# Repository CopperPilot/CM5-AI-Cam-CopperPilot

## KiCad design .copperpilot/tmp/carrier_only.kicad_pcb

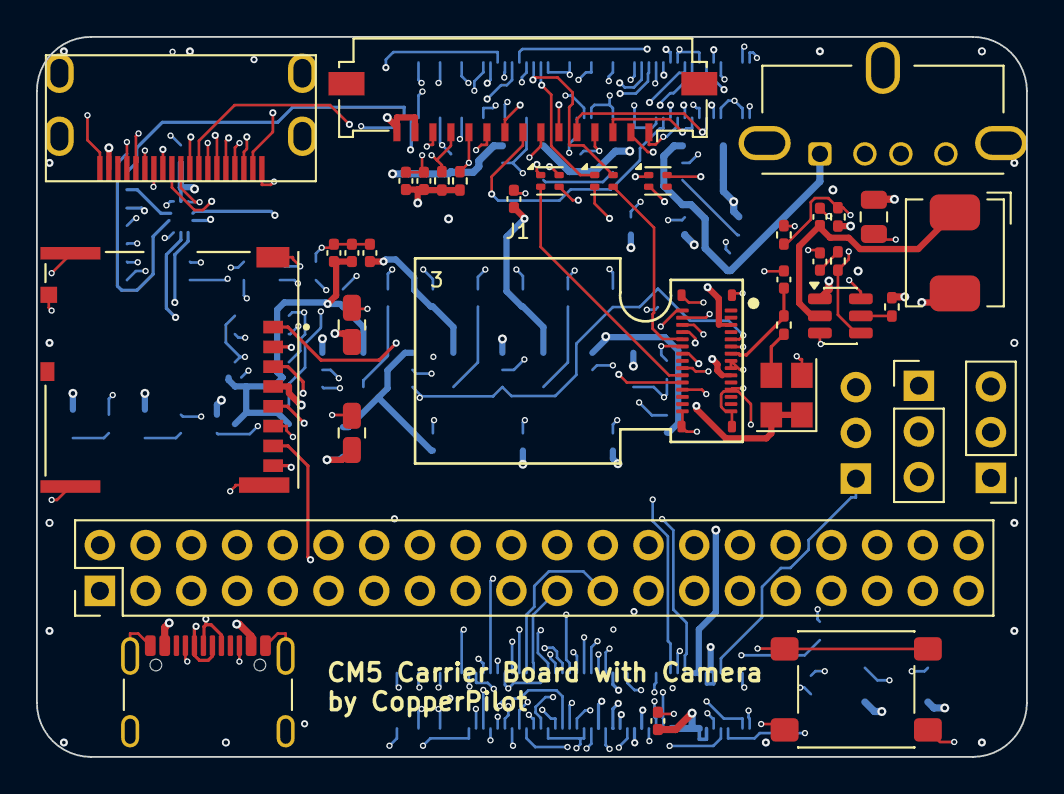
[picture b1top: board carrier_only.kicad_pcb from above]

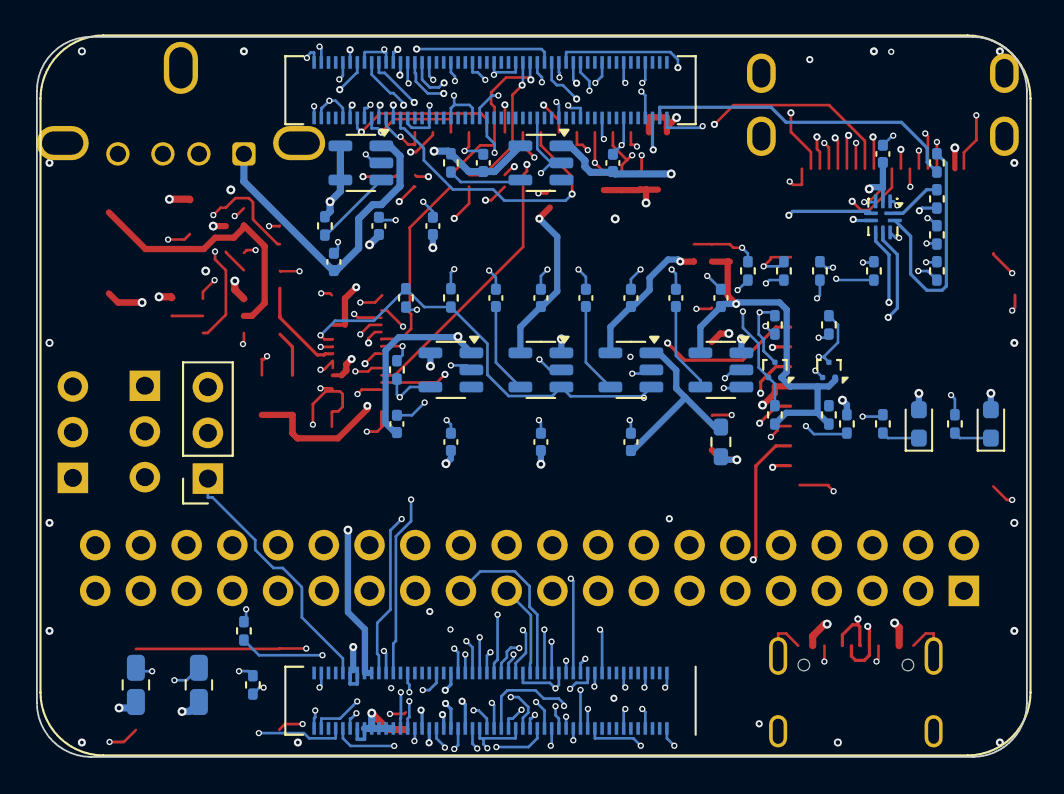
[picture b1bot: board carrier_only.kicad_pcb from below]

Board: 6 copper layers, 55.0 x 40.0 mm, 90 parts (54 on the bottom side), 118 nets.

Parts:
C1, C5, C12: 2.2uF; C_0402_1005Metric
C2, C6, C7, C8, C9, C15, C16, C21, C29, C30: 1uF; C_0402_1005Metric
C3, C10, C14: 100nF; C_0402_1005Metric
C4, C11, C22: 10uF; C_0805_2012Metric
C17, C18, C19, C23, C24, C27, C28, C31, C32: 0.1uF; C_0402_1005Metric
C20: 10pF; C_0402_1005Metric
C25, C26: 22uF; C_0805_2012Metric
DSI1: DSI_15P; Molex_200528-0150_1x15-1MP_P1.00mm_Horizontal
FB1: 120R; R_0603_1608Metric
H3, H4, H5: Conn_01x03; PinHeader_1x03_P2.54mm_Vertical
HDMI1: HDMI_Mini_C; HDMI_Mini-C_Molex_47151-0001
J1: Camera_Module_IMX219-D160
J2: USB_A_Vertical; MOLEX_USB_67298-4090
Key1: SW_Push_SPST; SW_SPST_PTS645Sx43SMTR92
L1, L2, L3: MCF1210BF2-900T01; L_CommonModeChoke_Coilank_ACM1210
L5: LED Red; LED_0603_1608Metric
L6: LED Green; LED_0603_1608Metric
L7: 4.7uH; L_Bourns_SRP5030CC
Module1: ComputeModule5-CM5; Raspberry-Pi-5-Compute-Module
PI1: Raspberry_Pi_40Pin_GPIO; PinHeader_2x20_P2.54mm_Vertical
Q1, Q2: DMG1012T; Texas_DRT-3
R1, R17, R22, R24, R29, R31, R32, R33: 0R; R_0402_1005Metric
R2, R3: 5.1k; R_0402_1005Metric
R4, R7, R35, R36: 4.7k; R_0402_1005Metric
R5, R8: 2.2k; R_0402_1005Metric
R10: 22R; R_0402_1005Metric
R11, R14, R30, R34: 10k; R_0402_1005Metric
R12, R13: 1k; R_0402_1005Metric
R15, R19, R20: 100k; R_0402_1005Metric
R16: 10R; R_0402_1005Metric
R21: 20k; R_0402_1005Metric
R28: 47k; R_0402_1005Metric
TF1: Micro_SD_Card_Det; SDCARD_MOLEX_503398-1892
Type_C1: USB_C_Receptacle_USB2.0_16P; USB_C_Receptacle_GCT_USB4105-xx-A_16P_TopMnt_Horizontal
U1: RT9193-28GB; SOT-23-5
U2: RT9193-18GB; SOT-23-5
U3: RT9013-12; SOT-23-5
U4, U7: DIO7003HCST5; SOT-23-5
U5: MP1658GTF-Z; TSOT-23-6
U6: FSUSB42MX; UQFN-10_1.4x1.8mm_P0.4mm
U8: STMPS2171STR; SOT-23-5
X1: OSC_24MHz; Crystal_SMD_3225-4Pin_3.2x2.5mm

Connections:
/1V2: C7.1, C15.1, J1.4, U3.5
/1V8: C6.1, C9.1, C16.1, J1.3, Q1.1, Q2.1, R5.1, R8.1, U2.5, X1.1, X1.4
/2V8: C2.1, C8.1, J1.10, U1.5
/BT_EN: Module1.91, R32.1
/CAM0_CLK_N: L3.4, Module1.140
/CAM0_CLK_P: L3.1, Module1.142
/CAM0_D0_N: L1.4, Module1.128
/CAM0_D0_P: L1.1, Module1.130
/CAM0_D1_N: L2.4, Module1.134
/CAM0_D1_P: L2.1, Module1.136
/CAM_FB1_OUT: C1.1, FB1.2, U1.1
/CAM_GPIO: Module1.97, R17.1
/CAM_GPIO': J1.5, R15.1, R17.2, U1.3, U2.3, U3.3
/CC1: R3.1, Type_C1.A5
/CC2: R2.1, Type_C1.B5
/CM5_1V8: H5.3, Module1.88, Module1.90
/CM5_3V3: C28.1, H5.1, Module1.84, Module1.86, U6.9
/CM5_5V: C4.1, C11.1, C17.1, C22.1, C23.1, C30.1, Module1.77, Module1.79, Module1.81, Module1.83, Module1.85, Module1.87, PI1.2, PI1.4, R14.2, R19.2, R34.2, Type_C1.A4, Type_C1.A9, Type_C1.B4, Type_C1.B9, U4.5, U5.1, U8.4, U8.5
/CSI_CLK_N: J1.26, L3.3
/CSI_CLK_P: J1.27, L3.2
/CSI_D0_N: J1.23, L1.3
/CSI_D0_P: J1.24, L1.2
/CSI_D1_N: J1.20, L2.3
/CSI_D1_P: J1.21, L2.2
/DSI1_CLK_N: DSI1.5, Module1.187
/DSI1_CLK_P: DSI1.6, Module1.189
/DSI1_D0_N: DSI1.8, Module1.175
/DSI1_D0_P: DSI1.9, Module1.177
/DSI1_D1_N: DSI1.2, Module1.181
/DSI1_D1_P: DSI1.3, Module1.183
/EEPROM_WP: Module1.20, R29.1
/GPIO2: Module1.58, PI1.3
/GPIO3: Module1.56, PI1.5
/GPIO4: Module1.54, PI1.7
/GPIO5: Module1.34, PI1.29
/GPIO6: Module1.30, PI1.31
/GPIO7: Module1.37, PI1.26
/GPIO8: Module1.39, PI1.24
/GPIO9: Module1.40, PI1.21
/GPIO10: Module1.44, PI1.19
/GPIO11: Module1.38, PI1.23
/GPIO12: Module1.31, PI1.32
/GPIO13: Module1.28, PI1.33
/GPIO14: Module1.55, PI1.8
/GPIO15: Module1.51, PI1.10
/GPIO16: Module1.29, PI1.36
/GPIO17: Module1.50, PI1.11
/GPIO18: Module1.49, PI1.12
/GPIO19: Module1.26, PI1.35
/GPIO20: Module1.27, PI1.38
/GPIO21: Key1.1, Module1.25, PI1.40, R11.1
/GPIO22: Module1.46, PI1.15
/GPIO23: Module1.47, PI1.16
/GPIO24: Module1.45, PI1.18
/GPIO25: Module1.41, PI1.22
/GPIO26: Module1.24, PI1.37
/GPIO27: Module1.48, PI1.13
/GPIO_VREF: H5.2, Module1.78, R4.1, R7.1
/HDMI0_CEC: HDMI1.14, Module1.151
/HDMI0_CLK_N: HDMI1.12, Module1.190
/HDMI0_CLK_P: HDMI1.11, Module1.188
/HDMI0_HOTPLUG: HDMI1.19, Module1.153
/HDMI0_SCL: HDMI1.15, Module1.200
/HDMI0_SDA: HDMI1.16, Module1.199
/HDMI0_TX0_N: HDMI1.9, Module1.184
/HDMI0_TX0_P: HDMI1.8, Module1.182
/HDMI0_TX1_N: HDMI1.6, Module1.178
/HDMI0_TX1_P: HDMI1.5, Module1.176
/HDMI0_TX2_N: HDMI1.3, Module1.172
/HDMI0_TX2_P: HDMI1.2, Module1.170
/HDMI_5V: C18.1, HDMI1.18, U4.1
/HDMI_5V_EN: R14.1, U4.4
/ID_SC: Module1.35, PI1.28
/ID_SD: Module1.36, PI1.27
/L5_K: L5.1, R12.1
/L6_K: L6.1, R13.1
/LED_G: Module1.21, R13.2
/MCLK: C20.1, J1.7, R10.2
/MP1658_BST: C24.2, R16.1, U5.4
/MP1658_BST_R: C21.1, R16.2
/MP1658_EN: R19.1, U5.5
/MP1658_FB: R20.2, R21.1, U5.6
/MP1658_SW: C24.1, L7.1, U5.2
/PI_BOOT: H4.1, Module1.93
/PI_GLOBAL_EN: H3.3, Module1.99
/PI_RUN: H3.1, Module1.92
/PWR_3V3: C5.1, C12.1, C19.1, C25.1, C26.1, C27.1, C31.1, DSI1.14, DSI1.15, FB1.1, L5.2, L6.2, L7.2, PI1.1, PI1.17, R11.2, R20.1, R35.1, R36.1, U2.1, U3.1, U7.5
/SCL0: DSI1.11, Module1.80, Q1.3, R4.2, R35.2
/SCL_1V8: J1.29, Q1.2, R5.2
/SDA0: DSI1.12, Module1.82, Q2.3, R7.2, R36.2
/SDA_1V8: J1.30, Q2.2, R8.2
/SD_3.3V: C32.1, TF1.4, U7.1
/SD_CLK: Module1.57, TF1.5
/SD_CMD: Module1.62, TF1.3
/SD_DAT0: Module1.63, TF1.7
/SD_DAT1: Module1.67, TF1.8
/SD_DAT2: Module1.69, TF1.1
/SD_DAT3: Module1.61, TF1.2
/SD_PWREN: Module1.75, R30.1, U7.4
/SD_VDD_Override: Module1.73, R1.1
/U1_BP: C3.1, U1.4
/U2_BP: C10.1, U2.4
/U3_BP: C14.1, U3.4
/USB0_B_N: R22.2, U6.2
/USB0_B_P: R24.2, U6.1
/USB0_ID: Module1.101, R33.1
/USB0_N: Module1.103, R22.1
/USB0_P: Module1.105, R24.1
/USBB_N: Type_C1.A7, Type_C1.B7, U6.4
/USBB_P: Type_C1.A6, Type_C1.B6, U6.5
/USBD0_N: J2.2, U6.6
/USBD0_P: J2.3, U6.7
/USB_5V: C29.1, J2.1, U8.1
/USB_FAULT: R34.1, U8.3
/USB_SEL: H4.3, R28.1, U6.10
/WIFI_EN: Module1.89, R31.1
/X1_OUT: R10.1, X1.3
GND: C1.2, C2.2, C3.2, C4.2, C5.2, C6.2, C7.2, C8.2, C9.2, C10.2, C11.2, C12.2, C14.2, C15.2, C16.2, C17.2, C18.2, C19.2, C20.2, C21.2, C22.2, C23.2, C25.2, C26.2, C27.2, C28.2, C29.2, C30.2, C31.2, C32.2, DSI1.1, DSI1.4, DSI1.7, DSI1.10, DSI1.13, H3.2, H4.2, HDMI1.1, HDMI1.4, HDMI1.7, HDMI1.10, HDMI1.13, HDMI1.SH, J1.6, J1.8, J1.9, J1.12, J1.15, J1.16, J1.19, J1.22, J1.25, J1.28, J1.SH, J2.4, J2.SH, Key1.2, Module1.1, Module1.2, Module1.7, Module1.8, Module1.13, Module1.14, Module1.22, Module1.23, Module1.32, Module1.33, Module1.42, Module1.43, Module1.52, Module1.53, Module1.59, Module1.60, Module1.65, Module1.66, Module1.71, Module1.74, Module1.98, Module1.107, Module1.108, Module1.113, Module1.114, Module1.119, Module1.120, Module1.125, Module1.126, Module1.131, Module1.132, Module1.137, Module1.138, Module1.144, Module1.150, Module1.155, Module1.156, Module1.161, Module1.162, Module1.167, Module1.168, Module1.173, Module1.174, Module1.179, Module1.180, Module1.185, Module1.186, Module1.191, Module1.192, Module1.197, Module1.198, PI1.6, PI1.9, PI1.14, PI1.20, PI1.25, PI1.30, PI1.34, PI1.39, R1.2, R2.2, R3.2, R12.2, R15.2, R21.2, R28.2, R29.2, R30.2, R31.2, R32.2, R33.2, TF1.6, TF1.9, TF1.11, Type_C1.A1, Type_C1.A12, Type_C1.B1, Type_C1.B12, Type_C1.S1, U1.2, U2.2, U3.2, U4.2, U5.3, U6.3, U6.8, U7.2, U8.2, X1.2

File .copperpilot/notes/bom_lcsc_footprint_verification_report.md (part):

# Comprehensive BOM, LCSC Sourcing, and Footprint Verification Report

**Project:** CM5 AI Camera Carrier Board (`CM5-AI-Cam-CopperPilot`)  
**Target Assembler:** JLCPCB PCBA / SMT Assembly  
**Audited Artifacts:**
- BOM: `jlcpcb_production/assembly/bom_jlcpcb.csv` (42 lines, 81 placed instances)
- CPL: `jlcpcb_production/assembly/cpl_jlcpcb.csv` (81 placed instances)
- Schematic: `CM5-AI-Cam-CopperPilot.kicad_sch` (91 non-power symbol instances)
- PCB: `CM5-AI-Cam-CopperPilot.kicad_pcb` (90 placed footprint instances)
- Footprint Library: `./CM5.pretty/` (63 footprint definitions)

---

## 1. Fatal Footprint Package Mismatches

Four critical components have fatal mechanical or land pattern incompatibilities between the physical component, the BOM part number, and the placed PCB footprint:

### 1.1 U5: MP1658GTF-Z (Buck Converter)
- **Schematic Reference / Value:** `U5`, `MP1658GTF-Z` (LCSC `C9900009837`)
- **Assigned PCB Footprint:** `CM5:TSOT-23-6`
- **Datasheet Reality:** Monolithic Power Systems (MPS) package code `GTF` is strictly **SOT-563** (1.60 × 1.20 mm body, 1.60 × 1.60 mm total footprint with leads, 0.50 mm lead pitch).
- **Physical Comparison:**
  | Dimension | MP1658GTF-Z (SOT-563) | Placed Footprint (TSOT-23-6) | Conflict Severity |
  |:---|:---|:---|:---|
  | **Lead Pitch** | 0.50 mm | 0.95 mm | **+90% pitch error** |
  | **Pad Center Span (X)** | 1.425 mm | 2.275 mm | **+0.85 mm excessive span** |
  | **Pad Dimensions** | 0.675 × 0.35 mm | 1.325 × 0.60 mm | **Massive oversize** |
- **Assembly Consequence:** The physical SOT-563 IC leads fall entirely into the central dead space between the TSOT-23-6 pads. The component cannot bridge the pads, making automated SMT or hand soldering impossible.
- **Remediation:** Replace footprint with `CM5:SOT-563` (already existing in `./CM5.pretty/SOT-563.kicad_mod`).

### 1.2 Q1, Q2: DMG1012T-7 (I2C Level-Shifter MOSFETs)
- **Schematic Reference / Value:** `Q1, Q2`, `DMG1012T` (LCSC `C20512`)
- **Assigned PCB Footprint:** `CM5:Texas_DRT-3`
- **Datasheet Reality:** Diodes Inc `DMG1012T-7` is packaged strictly in **SOT-523** (body 1.60 × 0.80 mm, overall span 1.60 mm, lead pitch 1.00 mm). The suffix `T` in Diodes Inc parts designates SOT-523.
- **Physical Comparison:**
  | Dimension | DMG1012T-7 (SOT-523) | Placed Footprint (Texas_DRT-3) | Conflict Severity |
  |:---|:---|:---|:---|
  | **Lead Pitch (P1-P2)** | 1.00 mm | 0.70 mm | **+43% pitch error** |
  | **Pad Span (Y)** | 1.29 mm | 0.85 mm | **+0.44 mm mismatch** |
  | **Pad Dimensions** | 0.51 × 0.40 mm | 0.30 × 0.30 mm | **Pads ~50% undersized** |
  | **Component Body** | 1.60 × 1.60 mm | 1.00 × 0.80 mm | **Part 1.6× larger than footprint** |
- **Assembly Consequence:** The physical SOT-523 transistor is ~160% the size of the Texas_DRT-3 land pattern. Solder paste will bridge across the minute 0.3 mm pads, or the transistor pins will hang outside the pads with zero solder fillet.
- **Remediation:** Replace footprint with `CM5:SOT-523` (already existing in `./CM5.pretty/SOT-523.kicad_mod`).

### 1.3 J2: USB-A Host Connector (Vertical vs Right-Angle)
- **Schematic Reference / Value:** `J2`, `USB_A_Vertical`
- **Assigned PCB Footprint:** `CM5:MOLEX_USB_67298-4090` (Vertical through-hole, Molex 105057-0001 equivalent)
- **Assigned BOM Part:** `C720523` -> **XUNPU USB-226-BRY**
- **Datasheet Reality:** XUNPU USB-226-BRY is a **Right-Angle (side-insertion)** through-hole USB-A receptacle. The PCB footprint is a **Vertical (top-insertion)** through-hole receptacle.
- **Physical Comparison:**
  | Feature | BOM Part (XUNPU USB-226-BRY) | PCB Footprint (MOLEX 67298-4090) |
  |:---|:---|:---|
  | **Insertion Axis** | Horizontal (Right-Angle) | Vertical (Straight) |
  | **Signal Pins** | 4 pins bent 90° | 4 straight pins inline at Y=0 (pitch 2.0/2.5 mm) |
  | **Shield Tabs** | 2 lateral side snap-in tabs | 3 triangular retention tabs (X=-3.07, +3.50, +10.07 mm) |
- **Assembly Consequence:** The pins and mechanical retention legs of the right-angle connector cannot mechanically align or insert into the vertical mounting holes on the PCB.
- **Remediation:** Update BOM to a genuine vertical through-hole USB-A connector (e.g. LCSC `C698207` or Molex `105057-0001`), or assign through-hole manual assembly with the correct vertical part.

### 1.4 Module1: Raspberry Pi Compute Module 5 Connector (CPL & BOM Multiplicity Defect)
- **Schematic Reference / Value:** `Module1`, `ComputeModule5-CM5`
- **Assigned PCB Footprint:** `CM5:Raspberry-Pi-5-Compute-Module` (200-pin monolithic footprint)
- **Assigned BOM Part:** `C597931` -> **Hirose DF40C-100DS-0.4V(51)** (Quantity = 1)
- **Datasheet Reality:** The Raspberry Pi CM5 requires **TWO independent 100-pin Hirose DF40 mezzanine connectors** separated by 33.92 mm center-to-center.
- **Assembly Consequence:**
  1. **BOM Shortage:** The BOM lists Quantity 1 of `C597931`, leaving the second 100-pin socket completely unpopulated.
  2. **CPL Centroid Collision:** Because `Module1` is a single monolithic KiCad component, `cpl_jlcpcb.csv` exports a single centroid at (72.8000, -61.4200) on B.Cu. This position corresponds to the dead air gap between the two connectors! An automated pick-and-place machine will attempt to drop a single 100-pin connector into the center void.
- **Remediation:** Split `Module1` into two schematic symbols and footprints (`J1A`, `J1B`) using `CM5:CONN_DF40C-100DS-0.4V51_HIR`. This automatically yields Quantity 2 of `C597931` in the BOM and two accurate placement centroids in the CPL.

---

## 2. BOM LCSC Part Number Verification

Verification of all 42 lines in `jlcpcb_production/assembly/bom_jlcpcb.csv` against component datasheets, pinout, and JLCPCB library:

| Row | Comment / Value | Designators | Qty | Assigned Footprint | LCSC Part # | Manufacturer & MPN | JLCPCB Class | Verification Status & Findings |
|:---:|:---|:---|:---:|:---|:---|:---|:---:|:---|
| 1 | 2.2uF | C1, C12, C5 | 3 | C_0402_1005Metric | C23733 | Samsung CL05A225MP5NRNC | Basic | **VERIFIED MATCH** (2.2uF 10V X5R 0402) |
| 2 | 100nF | C10, C14, C3 | 3 | C_0402_1005Metric | C1525 | Samsung CL05B104KO5NNNC | Basic | **VERIFIED MATCH** (100nF 50V X7R 0402) |
| 3 | 10uF | C11, C22, C4 | 3 | C_0805_2012Metric | C15850 | Samsung CL21A106KAYNNNE | Basic | **VERIFIED MATCH** (10uF 25V X5R 0805) |
| 4 | 1uF | C15, C16, C2, C21, C29, C30, C6, C7, C8, C9 | 10 | C_0402_1005Metric | C52923 | Samsung CL05A105KA5NQNC | Basic | **VERIFIED MATCH** (1uF 25V X5R 0402) |
| 5 | 0.1uF | C17, C18, C23, C24, C27, C28, C31, C32 | 8 | C_0402_1005Metric | C1525 | Samsung CL05B104KO5NNNC | Basic | **VERIFIED MATCH** (0.1uF 50V X7R 0402) |
| 6 | 10pF | C20 | 1 | C_0402_1005Metric | C32949 | Samsung CL05C100JB5NNNC | Basic | **VERIFIED MATCH** (10pF 50V C0G 0402) |
| 7 | 22uF | C25, C26 | 2 | C_0805_2012Metric | C45783 | Samsung CL21A226MAQNNNE | Extended | **VERIFIED MATCH** (22uF 25V X5R 0805) |
| 8 | DSI_15P | DSI1 | 1 | Molex_200528-0150_1x15-1MP_P1.00mm_Horizontal | C2914074 | HDGC 1.0K-FX-15PWB / Molex 200528-0150 | Extended | **VERIFIED MATCH** (15P 1.0mm pitch FPC) |
| 9 | 120R | FB1 | 1 | R_0603_1608Metric | C50843 | Fenghua CBG160808U121T | Basic | **VERIFIED MATCH** (120Ω @ 100MHz 0603 Bead) |
| 10 | Conn_01x03 | H3, H4, H5 | 3 | PinHeader_1x03_P2.54mm_Vertical | C49257 | BOOMELE 2.54-1*3P | Extended | **VERIFIED MATCH** (Requires TH hand assembly) |
| 11 | HDMI_Mini_C | HDMI1 | 1 | HDMI_Mini-C_Molex_47151-0001 | C2013978 | TE Connectivity 2013978-2 / Molex 47151-0001 | Extended | **SOURCING RISK** (Molex 47151-0001 obsolete; C2013978 out of stock) |
| 12 | IMX219_30P | J1 | 1 | Camera_Module_IMX219-D160 | C6539772 | Hirose DF37NB-30DS-0.4V(75) | Extended | **VERIFIED MATCH** (30P 0.4mm pitch mezzanine) |
| 13 | USB_A_Vertical | J2 | 1 | MOLEX_USB_67298-4090 | C720523 | XUNPU USB-226-BRY | Extended | **FATAL MISMATCH** (BOM is Right-Angle; Footprint is Vertical TH) |
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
